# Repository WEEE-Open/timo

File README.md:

# timo
TTY Integrata Massiva Operazionale

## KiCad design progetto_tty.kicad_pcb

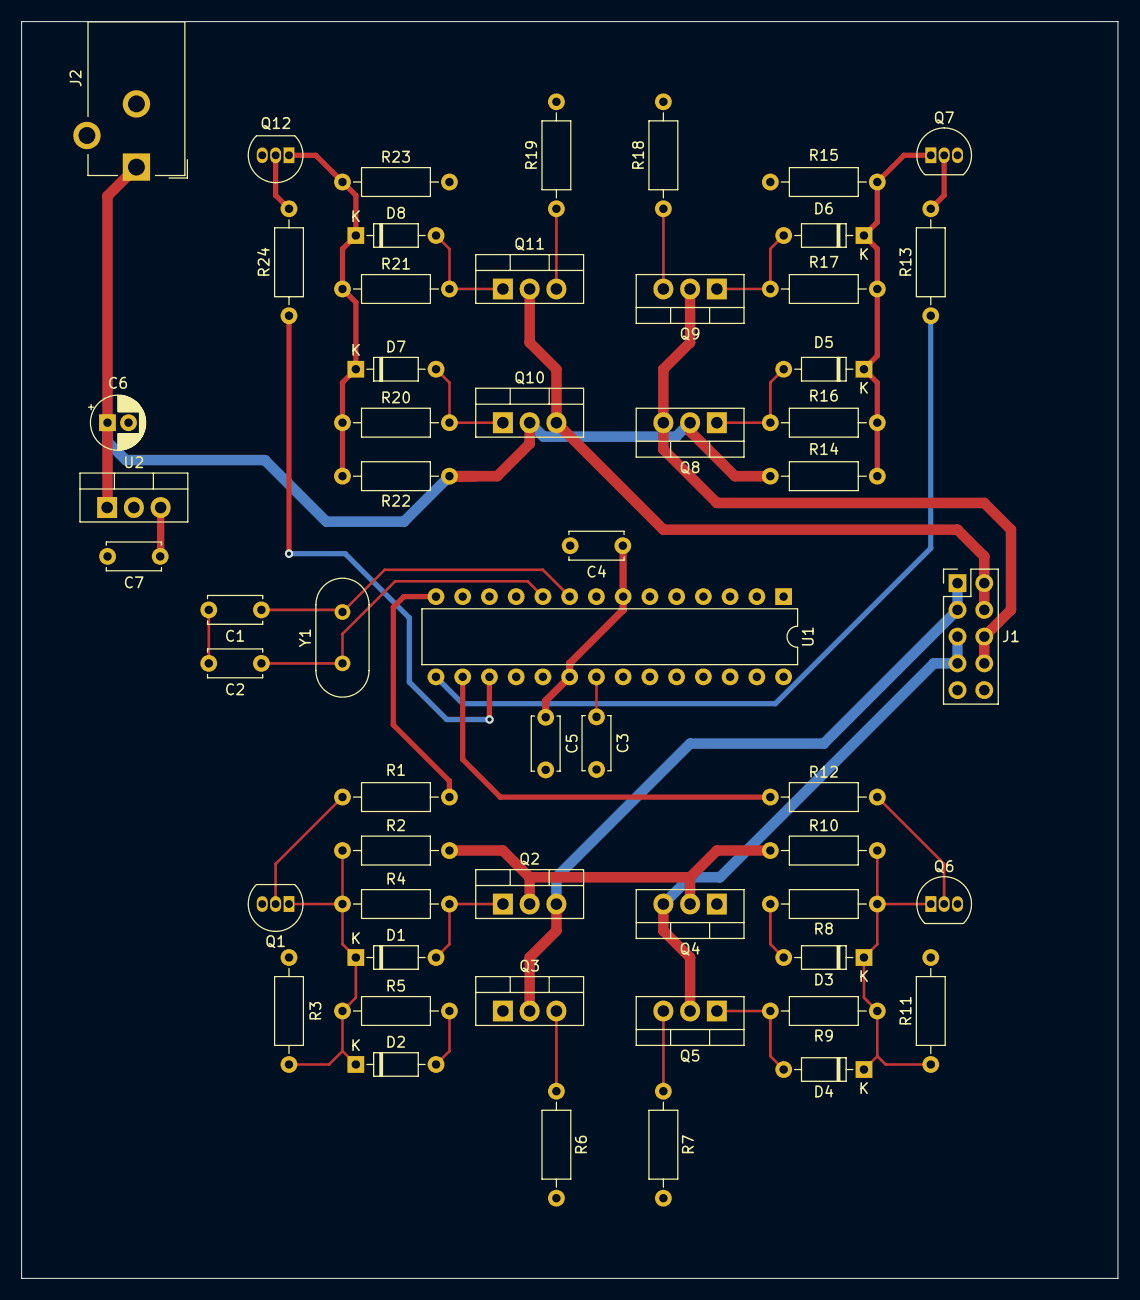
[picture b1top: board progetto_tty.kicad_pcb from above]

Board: 2 copper layers, 104.1 x 119.4 mm, 56 parts (0 on the bottom side), 32 nets.

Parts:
C1, C2: 22p; C_Disc_D5.0mm_W2.5mm_P5.00mm
C3, C4, C5, C7: 100n; C_Disc_D5.0mm_W2.5mm_P5.00mm
C6: 330n; CP_Radial_D5.0mm_P2.00mm
D1, D2, D3, D4, D5, D6, D7, D8: 1N4148; D_DO-35_SOD27_P7.62mm_Horizontal
J1: Conn_02x05_Odd_Even; PinHeader_2x05_P2.54mm_Vertical
J2: Conn_Coaxial_Power; BarrelJack_CUI_PJ-102AH_Horizontal
Q1, Q6, Q7, Q12: BC548; TO-92_Inline
Q2, Q4, Q8, Q10: IRF9540N; TO-220-3_Vertical
Q3, Q5, Q9, Q11: IRF540N; TO-220-3_Vertical
R1, R12, R13, R24: 22K; R_Axial_DIN0207_L6.3mm_D2.5mm_P10.16mm_Horizontal
R2, R10, R14, R22: 10K; R_Axial_DIN0207_L6.3mm_D2.5mm_P10.16mm_Horizontal
R3, R11, R15, R23: 1Meg; R_Axial_DIN0207_L6.3mm_D2.5mm_P10.16mm_Horizontal
R4, R5, R8, R9, R16, R17, R20, R21: 100; R_Axial_DIN0207_L6.3mm_D2.5mm_P10.16mm_Horizontal
R6, R7, R18, R19: 10; R_Axial_DIN0207_L6.3mm_D2.5mm_P10.16mm_Horizontal
U1: ATmega328P-P; DIP-28_W7.62mm
U2: L7805; TO-220-3_Vertical
Y1: 16MHz; Crystal_HC49-U_Vertical

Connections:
+5V: C4.1, C5.1, C7.1, U1.7 (VCC), U1.20 (AVCC), U2.3 (OUT)
+12V: C6.1, J1.2, J1.4, J1.6, J1.8, J2.1 (In), Q2.2 (D), Q4.2 (D), Q8.2 (D), Q8.3 (S), Q9.2 (D), Q10.2 (D), Q10.3 (S), Q11.2 (D), R2.2, R10.1, R14.2, R22.1, U2.1 (IN)
/D8: R1.1, U1.14 (PB0)
/D9: R13.1, U1.15 (PB1)
/D10: R12.1, U1.16 (PB2)
/D11: R24.1, U1.17 (PB3)
BLACK_1: J1.1, J1.3, Q2.3 (S), Q3.2 (D)
GND: C1.2, C2.2, C3.2, C4.2, C5.2, C6.2, C7.2, J2.2 (Ext), Q1.3 (E), Q6.3 (E), Q7.3 (E), Q12.3 (E), R3.2, R6.2, R7.2, R11.2, R15.2, R18.2, R19.2, R23.2, U1.8 (GND), U1.22 (GND), U2.2 (GND)
GREY_1: J1.5, J1.7, Q4.3 (S), Q5.2 (D)
unnamed: C1.1, U1.9 (XTAL1/PB6), Y1.2
unnamed: C2.1, U1.10 (XTAL2/PB7), Y1.1
unnamed: C3.1, U1.21 (AREF)
unnamed: D1.1 (K), D2.1 (K), Q1.1 (C), R2.1, R3.1, R4.1, R5.1
unnamed: D1.2 (A), Q2.1 (G), R4.2
unnamed: D2.2 (A), Q3.1 (G), R5.2
unnamed: D3.1 (K), D4.1 (K), Q6.1 (C), R8.1, R9.1, R10.2, R11.1
unnamed: D3.2 (A), Q4.1 (G), R8.2
unnamed: D4.2 (A), Q5.1 (G), R9.2
unnamed: D5.1 (K), D6.1 (K), Q7.1 (C), R14.1, R15.1, R16.1, R17.1
unnamed: D5.2 (A), Q8.1 (G), R16.2
unnamed: D6.2 (A), Q9.1 (G), R17.2
unnamed: D7.1 (K), D8.1 (K), Q12.1 (C), R20.1, R21.1, R22.2, R23.1
unnamed: D7.2 (A), Q10.1 (G), R20.2
unnamed: D8.2 (A), Q11.1 (G), R21.2
unnamed: Q1.2 (B), R1.2
unnamed: Q3.3 (S), R6.1
unnamed: Q5.3 (S), R7.1
unnamed: Q6.2 (B), R12.2
unnamed: Q7.2 (B), R13.2
unnamed: Q9.3 (S), R18.1
unnamed: Q11.3 (S), R19.1
unnamed: Q12.2 (B), R24.2

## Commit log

2022-07-19 Generated repository
2022-07-19 Small changes
    Add decoupling caps, disconnect AREF from 5V, modify H-bridge resistor values
2022-07-19 Replaced steppers with pin connector
